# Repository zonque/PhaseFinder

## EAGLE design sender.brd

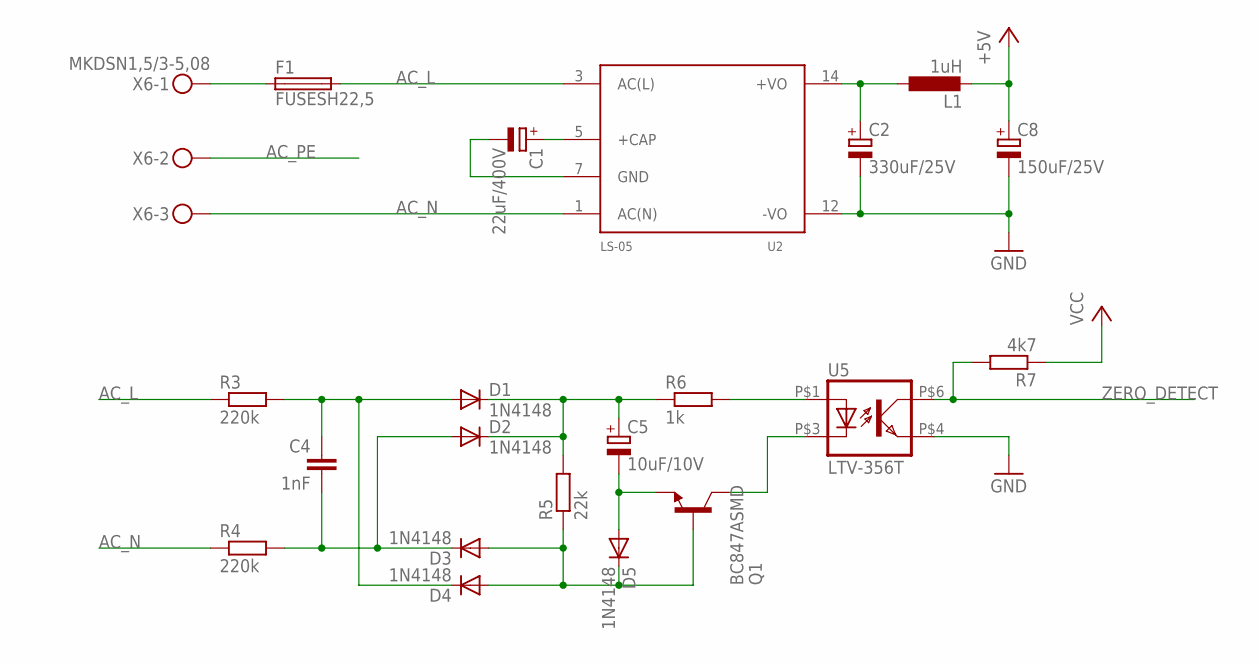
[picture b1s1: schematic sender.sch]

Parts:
C1: 22uF/400V; E7,5-16
C2: 330uF/25V; 150CLZ-1010
C4: 1nF; C050-050X075
C5: 10uF/10V; 153CLV-0505
C8: 150uF/25V; 153CLV-0810
D1, D2, D3, D4, D5: 1N4148; SOD323-W
F1: FUSESH22,5; SH22,5
L1: 1uH; L3225P
Q1: BC847ASMD; SOT23
R3, R4: 220k; R0603
R5: 22k; R0603
R6: 1k; R0603
R7: 4k7; R0603
U2: LS-05
U5: LTV-356T; SMD
X6: MKDSN1,5/3-5,08

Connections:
+5V: C8.+, L1.2
AC_L: F1.2, R3.1, U2.3 (AC(L))
AC_N: R4.1, U2.1 (AC(N)), X6.3
AC_PE: X6.2
GND: C2.-, C8.-, U2.12 (-VO), U5.P$4 (EMIT)
unnamed: F1.1, X6.1
unnamed: C2.+, L1.1, U2.14 (+VO)
unnamed: C1.+, U2.5 (+CAP)
unnamed: C4.1, D1.A, D4.C, R3.2
unnamed: C5.+, D1.C, D2.C, R5.2, R6.1
unnamed: C1.-, U2.7 (GND)
unnamed: C4.2, D2.A, D3.C, R4.2
unnamed: D3.A, D4.A, D5.C, Q1.1 (B), R5.1
unnamed: C5.-, D5.A, Q1.2 (E)
unnamed: R6.2, U5.P$1 (A)
unnamed: Q1.3 (C), U5.P$3 (C)
VCC: R7.1
ZERO_DETECT: R7.2, U5.P$6 (COL)

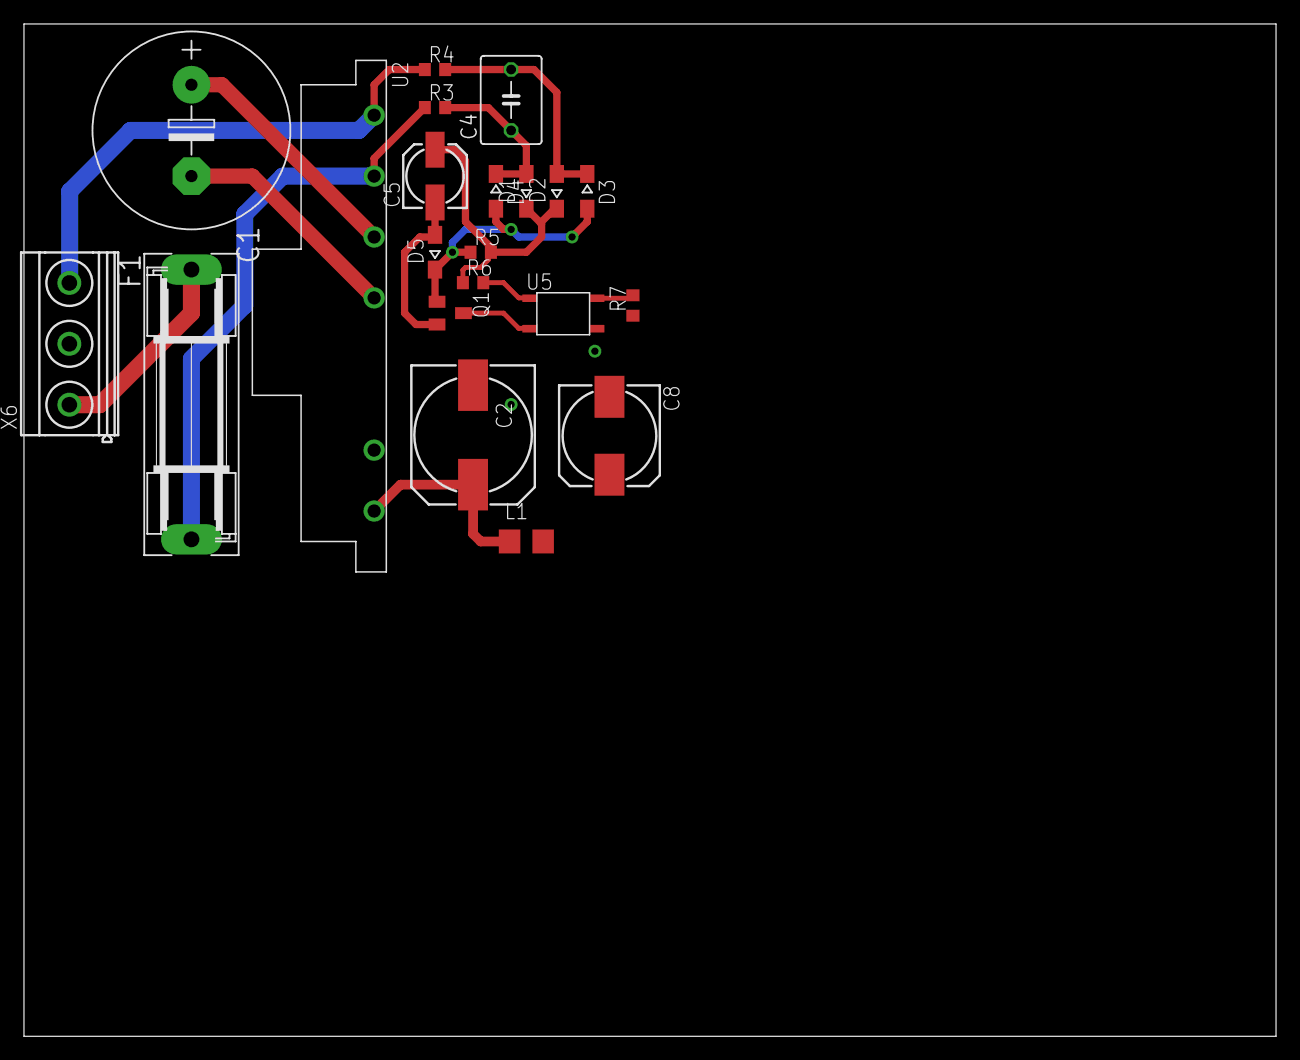
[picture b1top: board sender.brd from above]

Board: 2 copper layers, 104.4 x 84.4 mm, 21 parts (0 on the bottom side), 16 nets.
